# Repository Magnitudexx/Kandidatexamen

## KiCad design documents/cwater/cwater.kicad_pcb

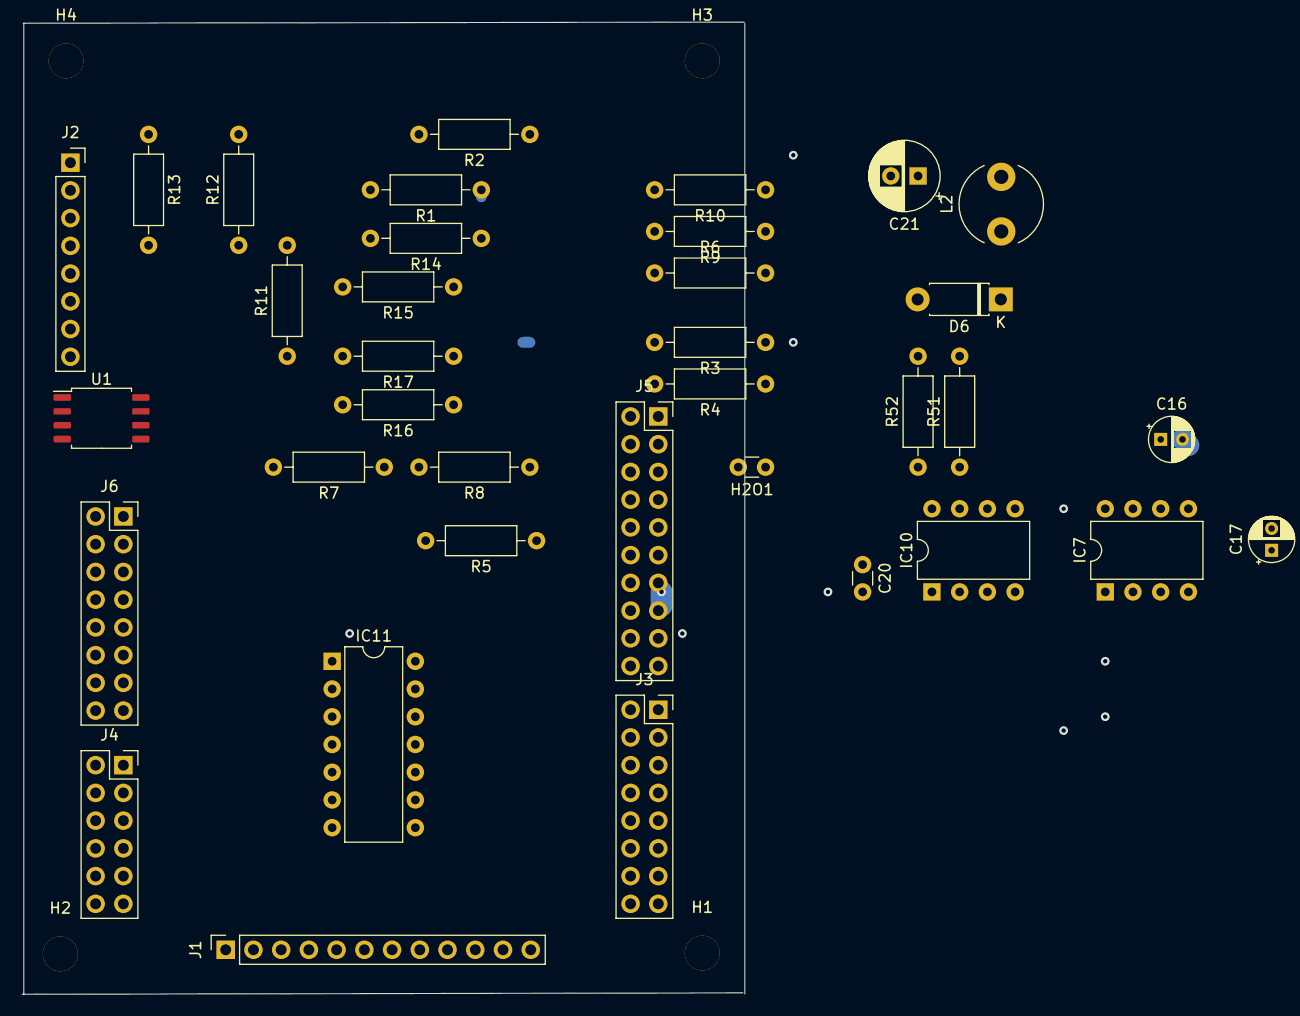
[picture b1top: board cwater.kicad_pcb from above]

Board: 2 copper layers, 66.2 x 89.1 mm, 40 parts (0 on the bottom side), 24 nets.

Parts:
C16, C17: 10u; CP_Radial_D4.0mm_P2.00mm
C20: 0.1u; C_Disc_D3.0mm_W1.6mm_P2.50mm
C21: 100u; CP_Radial_D6.3mm_P2.50mm
D6: 1N5818; D_DO-41_SOD81_P7.62mm_Horizontal
H1, H2, H3, H4: MountingHole_Pad; MountingHole_3.2mm_M3
H2O1: xxx; C_Disc_D3.0mm_W1.6mm_P2.50mm
IC7: MAX603; DIP-8_W7.62mm
IC10: MAX635; DIP-8_W7.62mm
IC11: LP324N; DIP-14_W7.62mm
J1: Conn_01x12; PinSocket_1x12_P2.54mm_Vertical
J2: Conn_01x08; PinSocket_1x08_P2.54mm_Vertical
J3, J6: Conn_02x08_Top_Bottom; PinSocket_2x08_P2.54mm_Vertical
J4: Conn_02x06_Top_Bottom; PinSocket_2x06_P2.54mm_Vertical
J5: Conn_02x10_Top_Bottom; PinSocket_2x10_P2.54mm_Vertical
L2: 22uH; L_Radial_D7.5mm_P5.00mm_Fastron_07P
R1, R2, R3, R4, R7, R8, R9, R10: 270k; R_Axial_DIN0207_L6.3mm_D2.5mm_P10.16mm_Horizontal
R5, R6: 86; R_Axial_DIN0207_L6.3mm_D2.5mm_P10.16mm_Horizontal
R11, R12: 10k; R_Axial_DIN0207_L6.3mm_D2.5mm_P10.16mm_Horizontal
R13: 20k; R_Axial_DIN0207_L6.3mm_D2.5mm_P10.16mm_Horizontal
R14, R16: 300k; R_Axial_DIN0207_L6.3mm_D2.5mm_P10.16mm_Horizontal
R15, R17: 100k; R_Axial_DIN0207_L6.3mm_D2.5mm_P10.16mm_Horizontal
R51: 30k; R_Axial_DIN0207_L6.3mm_D2.5mm_P10.16mm_Horizontal
R52: 166k; R_Axial_DIN0207_L6.3mm_D2.5mm_P10.16mm_Horizontal
U1: AT45DB161D-SU; SOIC-8_5.275x5.275mm_P1.27mm

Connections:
+5VA: C16.1, IC7.8, IC11.4, J1.11
/-7.2V: C21.2, D6.2, IC11.11, J1.12, R52.2
GND: C16.2, C17.2, C20.2, C21.1, H1.1, H2.1, H3.1, H4.1, IC7.5, IC7.6, IC10.1, IC10.3, IC10.4, J1.7, J1.8, J1.9, L2.2, R11.1, R15.2, R17.2
unnamed: C17.1, IC7.1, IC7.4, IC10.6, J1.10
unnamed: C20.1, IC10.7, R51.1
unnamed: D6.1, IC10.5, L2.1
unnamed: H2O1.1, IC11.10, J1.5, R6.2
unnamed: H2O1.2, J1.6, R5.1
unnamed: IC10.8, R51.2, R52.1
unnamed: IC11.1, IC11.12, R2.1, R6.1
unnamed: IC11.2, R1.1, R2.2
unnamed: IC11.3, R14.1, R15.1
unnamed: IC11.5, R16.1, R17.1
unnamed: IC11.6, R7.1, R8.2
unnamed: IC11.7, R5.2, R8.1
unnamed: IC11.8, J1.1, R4.2
unnamed: IC11.9, R3.2, R4.1
unnamed: IC11.13, R9.2, R10.1
unnamed: IC11.14, R3.1, R10.2
unnamed: J1.2, R16.2
unnamed: J1.3, R14.2
unnamed: J1.4, R13.2
unnamed: R1.2, R7.2, R11.2, R12.1
unnamed: R9.1, R12.2, R13.1

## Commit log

2023-02-15 added data from some days
2023-02-15 wednesday feb 15
2023-02-17 thursday feb 16
2023-02-17 friday feb 17
2023-02-20 monday feb 20
2023-02-22 tuesday feb 21
2023-02-22 twednsday feb 22
2023-02-23 thursday feb 23
2023-02-27 friday feb 24
2023-02-28 monday feb 27
2023-03-01 tuesday feb 28
2023-03-02 wednesday mar 1
2023-03-02 thursday mar 2
2023-03-06 friday mar 3
2023-03-07 mondayy mar 6
2023-03-08 tuesday mar 7
2023-03-08 wednesday mar 8
2023-03-10 thursday mar 9
2023-03-10 fridday mar 10
2023-03-14 monday mar 13
2023-03-15 tuesday mar 14
2023-03-17 wednesday mar 15
2023-03-17 friday mar 17
2023-03-22 monday mar 20 and tuesday
2023-03-23 wednesday mar 22
2023-03-24 thursday mar 23
2023-03-24 friday mar 24
2023-03-27 monday mar 27
2023-03-27 added documentation folder
2023-03-27 arduino embedded folder and example
2023-03-28 Added uart library
2023-03-29 added uart actually
2023-03-29 tuesday mar 28
2023-03-31 wednesday and thursday mar 30-31
2023-03-31 friday mar 31
2023-04-04 monday mar 3
2023-04-05 tuesday wednesday apr 4-5
2023-04-10 noPWVSÄD
2023-04-11 monday apr 10
2023-04-12 tuesday apr 11
2023-04-13 wednesday apr 12
2023-04-14 thursday apr 13
2023-04-17 friday apr 14
2023-04-17 Bluetooth added and tested
2023-04-17 memory and spi added
2023-04-18 monday apr 17
2023-04-19 tuesday apr 18
2023-04-20 wednesday apr 19
2023-04-21 thursday apr 20
2023-04-24 friday apr 21
2023-04-26 monday apr 24
2023-04-27 wednesday apr 27
2023-04-27 thursday apr 28
2023-05-02 ed feapr 28
2023-05-03 tuesday may 2
2023-05-04 wednesday may 3
2023-06-12 prepare for reinstallation
